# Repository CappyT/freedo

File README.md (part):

# freedo

A local coordinator for tado V3+ 868 MHz heating devices, with a Home Assistant integration.

This is heavily AI-assisted work. The code and the documentation were written largely with AI assistance, under the direction of the project owner. Behavior was checked with automated tests, and on a real plant only where the [Status](#status) section says so.

## Contents

- [What it is](#what-it-is)
- [Status](#status)
- [Scope and limits](#scope-and-limits)
  - [Supported devices](#supported-devices)
- [Compared with the tado cloud and HomeKit](#compared-with-the-tado-cloud-and-homekit)
- [Requirements](#requirements)
- [Install](#install)
- [First setup](#first-setup)
- [Dashboard](#dashboard)
- [Features](#features)
- [Safety](#safety)
- [Community](#community)
- [Documentation](#documentation)
- [Development](#development)
- [Legal](#legal)
- [Licence](#licence)

## What it is

freedo replaces the tado internet bridge for the radiator valves and wall thermostats that it
coordinates. The coordinator is a Go daemon. It talks over a serial link to an ESP32 with a CC1101
radio, and it serves a local HTTP API. A Home Assistant integration uses that API. The daemon
keeps the plant under local control, with no cloud.

freedo is not a way to use the tado app or the tado cloud. See [Scope and limits](#scope-and-limits).

freedo is not affiliated with tado. tado is a trademark of its owner. This project uses the
name only to describe which devices it works with. See [Legal](#legal) for the legal basis of the
project.

## Status

freedo is experimental. Expect bugs, and keep a way to control the heating by hand.

Tested on a real plant (one plant, one ESP32 development board with one CC1101 module):

- Reception and decoding of device reports (temperature, demand, boiler values, battery), and the MAC and CSL
  exchange with the bridge firmware.
- Setpoint, boost and return-to-program writes to a valve.
- Home and away: in use on the plant, and the valves follow.
- A weekly schedule: the rooms follow its blocks, and a schedule edited in the dashboard reaches the valves.
- The child lock of a valve: in use on the plant.
- Hot water on, off and temperature writes to the wall thermostat.
- A fixed flow limit, read back from the boiler through the OpenTherm values the thermostat reports.
- Identify on a valve and on the wall thermostat.
- The display orientation and the change notice of a valve.
- The motor calibration, on one valve.
- The temperature correction in the modes `config` and `dbg2`, on one valve.
- A window state that the coordinator sets, on one valve.
- A window that the wall thermostat detected: its report, the block that reaches the thermostat and the
  valve of the same room, the close after the window time, and a reset that ends the window before that
  time. No window that a valve detected was seen: with one sample each 10 to 16 minutes, a valve did not
  report an open window in 40 minutes.
- The warning for a valve that is not mounted. It raised no fault alert, and it cleared after the valve
  was mounted.
- Pairing one valve through the API: the button press that makes the valve leave, the removal from the
  installation, the pair window of the bridge firmware, the declaration of a device that the installation
  did not hold, the `d/pair` command and the serial that the daemon learns from the device. The valve
  works in its zone again. A remote leave command was tried on that valve and had no effect.
- Pairing the same valve from the dashboard, two times. The last version of the page Add device, with no
  default room and with the end state, did not run on the plant.
- On the page Rooms and devices: a room created, its options saved and the room deleted, a device moved
  from No room to a room, a device removed, and a valve restarted. The valve joined again by itself about
  40 seconds after the command.
- The add-on freedo beta: the move from the add-on freedo, with the copy of the state that the add-ons
  made by themselves up to 0.7.0. Every device talked to the beta add-on in three minutes. The return
  to the add-on freedo did not run with that copy.
- The backup of the dashboard: a download as a Home Assistant administrator with no token, a restore
  of that file in the same add-on, and the return from freedo beta to the add-on freedo with a
  restore there. The daemon kept the replaced state, restarted by itself, waited 250 seconds and
  talked to every device again with no decryption error. The countdown that the dashboard shows
  during that wait did not run on a plant.
- The read of the firmware version of each device.
- freedo runs as the only coordinator of that plant, as a Home Assistant add-on with the integration.
  The devices of that plant were not paired from scratch, apart from one valve.
- The dashboard commands for setpoint, boost, off, home and away, and the programs.

Tested only with automated tests and synthetic fixtures:

- Away temperatures, away programs and the end rule `until_auto_change`.
- A network that starts with no paired device, and the pairing of a wall thermostat.
- A window that a valve detects.
- The Router Advertisement gateway and DNS addresses (`router_gateway`, `router_dns`) and the zone
  configuration of a heating zone with no circuit.
- A schedule document with several day programs, the program profiles and the offline schedule
  (devices run the program alone).
- Firmware transfer to a device. No block was ever sent on air.
- Early start, the weather curves (your own and the default curve), automatic flow adaptation, the
  external room temperature, the automatic correction and the controller gain suggestion.
- The energy and gas estimate against the gas meter of the plant, over 8 days: the meter counted
  7.07 m3 and the estimate 7.38 m3, 4.4 % high. The daemon learned a correction factor of 0.958. The
  meter also counts any other gas user on it. A third reading checks that the factor holds.
- The web dashboard. `npm test` covers the API client and the schedule editor logic. `npm run prefix-check`
  and `npm run ui-check` start the daemon with no radio and a seeded synthetic installation. They open each
  page in headless Chrome under a path prefix, and drive the schedule editor, the presence switch, the
  child lock, Turn off, the profiles, the rename of a device, the page Rooms and devices (a room, a
  pairing, a move, a removal, a restart, a circuit), the options of a room, the boiler fault codes and the
  first setup on an empty database. The page First setup did not run on a plant that starts empty.
- The boiler fault codes in the dashboard and in Home Assistant. No real boiler fault was seen.
- In the integration: the reload after a change of the installation, the service `freedo.pair` and the
  event entity Alert.
- The six blueprints: presence, season profile, alert notification, distance setback, auxiliary heat and
  valve exercise.

No record covers a long run or a long outage of the coordinator.

## Scope and limits

- freedo replaces the tado internet bridge and the tado cloud for the devices it coordinates.
  It does not connect to the tado cloud in place of the bridge. The tado app does not work with a
  plant that freedo runs. This is out of scope.
- Device firmware updates: whether freedo can support them is under evaluation. If it does, you
  supply the firmware images. The project distributes none. The daemon has a transfer route that
  no test on air has used.
- An existing tado plant pairs to freedo from scratch. Each device leaves the commercial bridge and
  joins the network of freedo. The pairing ran on air for one valve. Only automated tests cover a
  network that starts with no paired device. You lose the tado app and the cloud functions for those
  devices. The
  rooms and schedules that you set in the tado app do not move to freedo. You describe the rooms again
  in the dashboard or through the API, and the schedules in the dashboard, Home Assistant or the API. To go back,
  pair the devices to the tado bridge again. That procedure belongs to the tado bridge and is not
  documented or tested here. freedo has no leave command and no remote detach. A device leaves its
  network only when you hold its button.
- A setup import from the tado cloud is planned: rooms, schedules and settings. The devices still pair from
  scratch. It is not available.
- Supported hardware: the valves and the wall thermostats of the V3+ line. Other device types
  (wireless receiver, extension kit, wireless sensor) are not supported, because no capture of
  them exists. See [Supported devices](#supported-devices) for the other tado lines.
- A circuit needs a wall thermostat as its heat source. A heating zone with no circuit gets a zone
  configuration without the circuit tag and without the heat source among the members. No device has
  run this configuration, and the install check warns about such a zone. A plant of valves without a
  wall thermostat is not supported yet.
- The boiler energy estimate needs a boiler that reports its modulation over OpenTherm. A boiler on a
  relay has no estimate yet.
- Geofencing, push notifications and multiple users are not part of the daemon. Home Assistant provides
  them. HomeKit is not implemented.

### Supported devices

freedo replaces the tado Internet Bridge IB01 and pairs each device to its own network. The device
models come from the tado article
[What is a tado° Starter Kit, and what are the differences between versions?](https://support.tado.com/en/articles/3403569-what-is-a-tado-starter-kit-and-what-are-the-differences-between-versions)

| Line | Sold | Devices | tado bridge | freedo |
|---|---|---|---|---|
| V1 | 2012-2014 | Box BX02, temperature sensor TS02 | Gateway GW01 | Not supported: a different system. |
| V2 | 2014-2016 | Smart Thermostat RU01, extension kit BU01 | Bridge GW02 | Not tested. Probably the same radio protocol, see [#25](https://github.com/CappyT/freedo/issues/25). |
| V3 | 2016-2018 | Smart Thermostat RU01, Smart Radiator Thermostat VA01 | Internet Bridge IB01 | Not tested. Probably works: it uses the same bridge as V3+. |
| V3+ | since 2018 | Wired Smart Thermostat RU02, Smart Radiator Thermostat VA02, Wireless Receiver BR02/BP02, Wireless Temperature Sensor SU02 | Internet Bridge IB01 | Valves and wired thermostat supported. Wireless receiver and sensor not supported. |
| tado X | since 2024 | RU04, RU05, VA04, SU04, SU05 and others | Bridge X IB02 | Not supported: Thread and Matter use a different radio. |

V2 is probable because tado documents a swap from the GW02 to the IB01 in which the installed
devices reconnect by themselves, and because tado sold the same RU01 with both bridges. Nobody has
tested a RU01 with freedo yet. The RU01 drives the boiler through the extension kit BU01, while
freedo knows the RU02, which drives the boiler over OpenTherm by itself.

## Compared with the tado cloud and HomeKit

The table compares three ways to run a V3+ plant:

- **tado cloud**: the tado Internet Bridge with the tado app. Some automations need the Auto-Assist
  subscription.
- **HomeKit**: the tado Internet Bridge with no internet access. Apple Home or the Home Assistant
  integration HomeKit Device controls it. The tado app does not work in this setup.
- **freedo**: this project, in place of the tado Internet Bridge.

The values in the cells:

- **Yes**: the setup has the function.
- **Auto-Assist**: the tado cloud has the function only with the subscription.
- **Automation**: you build the function yourself, with an Apple Home or Home Assistant automation or a
  third-party integration.
- **Blueprint**: a Home Assistant blueprint that freedo ships.
- **Home Assistant**: a standard function of Home Assistant gives it, with no automation.
- **Partial**: a part of the function is missing. The cell says which part.
- **No**: the setup does not have the function.

The tado columns come from the tado articles
[How does tado° work with Apple HomeKit?](https://support.tado.com/en/articles/3387320-how-does-tado-work-with-apple-homekit),
[What is Auto-Assist?](https://support.tado.com/en/articles/3387221-what-is-auto-assist) and
[What are Quick Actions?](https://support.tado.com/en/articles/4996736-what-are-quick-actions-for-tado-v3).
[Features](#features) gives the test status of each freedo function.

| Function | tado cloud | HomeKit | freedo |
|---|---|---|---|
| Room temperature, humidity and target | Yes | Yes | Yes |
| Off, heat and resume the schedule | Yes | Yes | Yes |
| End rule of a manual change: timer, next block, next automatic change | Yes | Automation. A HomeKit change stays until the schedule resumes. | Yes |
| Boost | Yes, all rooms for 30 minutes | Automation | Yes, one zone or all zones |
| Weekly schedule | Yes | Automation. The schedule set before keeps running, but you cannot change it. | Yes |
| Away schedule for each zone | No | Automation | Yes |
| Program profiles, for example summer and winter | No | Automation | Yes |
| Home and away, with an away temperature for each zone | Yes | Automation | Yes |
| Geofencing | Auto-Assist. Without it, the app asks you to switch. | Automation | Blueprint |
| Preheat before arrival | Auto-Assist | Automation | Blueprint. It reads the distance, not the travel time. |
| Early start | Yes | No | Yes |
| Open window detection | Yes. Without Auto-Assist, the app asks you to switch the heating off. | Automation, with a contact sensor | Yes, from the valves or from a contact sensor |
| Hot water: on, temperature, schedule | Yes | No | Yes |
| Room temperature from another sensor | No | Automation, with a third-party integration | Yes |
| Auxiliary heat from another climate device | No | Automation | Blueprint |
| Child lock, temperature offset, valve calibration, identify | Yes | No | Yes |
| Flow temperature limit | Yes | No | Yes |
| Flow temperature from the weather | Auto-Assist | No | Yes, with a local curve and controller |
| Boiler data and fault codes | Partial. Care & Protect tells you that the boiler has a fault, with no fault code. | No | Yes. OpenTherm now, the other boiler buses when their integration is complete. |
| Energy and gas report | Auto-Assist | No | Yes, from the boiler modulation, corrected by meter readings |
| History | 1 day. 13 months with Auto-Assist. | Home Assistant, with no heating report | Yes, in the daemon and in Home Assistant |
| Air comfort | Auto-Assist, with outdoor air freshness | No | Partial. No outdoor air freshness. |
| Alerts: low battery, device offline, open window | Yes | Automation | Blueprint |
| Several users | Yes | Yes, Apple Home sharing or Home Assistant users | Yes, the Home Assistant users |
| Voice control | Yes: Alexa, Google Assistant, Siri | Yes: Siri | Home Assistant |
| Remote access | Yes | Partial. It needs a home hub (Apple TV, HomePod, iPad) or Home Assistant. | Home Assistant |
| Works without internet | No. The app and the automations need the cloud. | Yes | Yes |
| Subscription | Auto-Assist, for the automations | No | No |
| Rooms, devices and pairing | Yes | No | Yes. Every device pairs again from scratch. |
| Device firmware updates | Yes | No | No |
| Supported devices | All V3+ devices | The heating and cooling rooms of the bridge | V3+ valves and wired wall thermostat |
| Extra hardware | No | No | An ESP32 with a CC1101 radio |
| Maturity | Commercial product | Commercial product | Experimental |

## Requirements

- Radio hardware: an ESP32 with a CC1101 module on a USB port, flashed with the bridge firmware
  in [`firmware/cc1101_bridge`](firmware/cc1101_bridge/README.md). Each release attaches the
  firmware image: see [Flash a released image](firmware/cc1101_bridge/README.md#flash-a-released-image).
  This firmware is almost completely AI-generated. See the [notice](firmware/cc1101_bridge/README.md)
  in its README: it ran on one ESP32 development board with one CC1101 module only.
- A radio board design for the bridge exists in [`hardware/radio`](hardware/radio/README.md). This PCB design is
  almost completely AI-generated and is not tested. See the [notice](hardware/radio/README.md) before you use it.
- A Home Assistant installation (2026.8 or later) or a host that runs a container.
- Go, if you build from source. The version is in `go.mod`.

Use one coordinator per radio network. Switch the commercial bridge off before freedo transmits.

## Install

<details>
<summary><strong>Info installation method</strong></summary>
The freedo service can run as a Home Assistant Add-on (recommended) or a standalone Docker container. 
Both use the same Home Assistant integration.

</details>
Install freedo (Add-On or Docker)

<table>
<tr>
<td width="50%" valign="top">

<details>
<summary><strong>Home Assistant Add-on (recommended)</strong></summary>

The easiest way to run freedo is directly as a Home Assistant Add-on (called an App in recent Home Assistant releases).

1. Add the freedo repository

   Alternative manually:
    <details>
    - Go to **Settings → Add-ons → Add-on Store**.
    - Add Repositories **https://github.com/CappyT/freedo**
    </details>
3. Install and configure freedo

    - Go to **Settings → Add-ons → Add-on Store**.
    - Search for **freedo** and install it.
    - Go to **freedo → Configuration**.
    - Enable **Show unused optional configuration options**.
    - Select the ESP32 serial port and click **Save**.
    - Go to **Info** and start freedo with **Protection Mode enabled**.

    The add-on starts in dry-run mode.

</details>

</td>
<td width="50%" valign="top">

<details>
<summary><strong>Standalone Docker container</strong></summary>

Run the freedo service independently of Home Assistant.

This is useful if you run Home Assistant in a container, on a separate machine or without the Home Assistant Supervisor.

The image ghcr.io/cappyt/freedo is available for linux/amd64 and linux/arm64.

1. Prepare the configuration

    sh
    cp docker-compose.example.yml docker-compose.yml
    openssl rand -hex 32 > freedo_api_token

2. Configure the container

    Before starting, edit docker-compose.yml and configure:
    
    The ESP32 serial device.
    The serial device group ID.
    The time zone (TZ).
    
    Without TZ, the container runs in UTC and the devices receive a UTC offset of 0.

3. Start the container

    sh
    docker compose up -d

The container starts in dry-run mode.

For volume configuration, time zone settings and building from source, see docs/OPERATION.md.

</details>

</td>
</tr>
</table>

<details>
<summary><strong>Install Home Assistant Integration (required for both installation methods)</strong></summary>

1. Add the freedo repository

    Alternative manually:

    <details>
    <summary><strong>Home Assistant 2026.11 and newer (Marketplace)</strong></summary>
    
    Open Settings → Marketplace.
    Add https://github.com/CappyT/freedo as an Integration.
    
    </details>
    
    <details>
    <summary><strong>Home Assistant versions before 2026.11 (HACS)</strong></summary>
    
    Open HACS → menu → Custom repositories.
    Enter https://github.com/CappyT/freedo.
    Select Integration and add the repository.
    
    </details>

2. Download and install freedo integration

    - Go to **HACS / Marketplace → Integrations**.
    - Search for **freedo** and click **Download**.
    - Restart Home Assistant.

4. Connect to the freedo integration with freedo(Add-On or Docker) 

    Home Assistant Add-on:
       Confirm the automatic discovery notification. It provides the host, port and token.
    Docker container:
       Go to Settings → Devices & services → Add integration → freedo. Enter the host, port and API token manually.

</details>

<details>
<summary><strong>Home Assistant Blueprints (optional)</strong></summary>

Import the available freedo automations directly into Home Assistant:

| Blueprint | Import |
|---|---|
| Notifications and alerts (including low battery) |  |
| Presence Away |  |
| Season Profile |  |
| Distance Setback |  |
| Auxiliary Heat |  |
| Valve Exercise |  |

</details>

<details>
<summary><strong>Stable and experimental versions</strong></summary>

The freedo add-on and integration follow two release channels:

Stable: Tags vX.Y.Z. The freedo add-on and HACS offer these versions by default.
Experimental: Pre-release tags such as vX.Y.Z-beta.N, which receive less testing on a real plant.

HACS offers experimental integration versions when beta versions are enabled for the freedo repository.

The repository also provides a second add-on, freedo beta, which runs experimental versions. It has its own data.

To move between the stable and beta add-ons:

Create a backup in the Settings page of the currently installed add-on.
Stop the currently running add-on.
Start the other add-on.
Restore the backup there.

The same procedure applies when switching back. The two add-ons must never run at the same time.

See addon-beta/DOCS.md for details about switching between versions.

Pre-release container images also carry the corresponding version tag and beta suffix.

</details>

Additional documentation
addon/DOCS.md – Add-on options, data and backups.
addon-beta/DOCS.md – Beta add-on and migration.
docs/OPERATION.md – Docker configuration and operation.
custom_components/freedo/README.md – Integration entities, services and blueprints.

## First setup

The page First setup of the [dashboard](#dashboard) shows these steps with their live state.

1. Start the daemon in dry-run and read its log.
2. Check `GET /api/health`. The field `mode` must be `live`. The field `calibrated` turns `true` once
   the radio has calibrated itself on the frames of the first paired device; until then the radio works
   on FSCTRL0 0x34, the start register. See [Radio calibration](docs/OPERATION.md#radio-calibration). The field `timezone.name` must be the
   time zone of the plant. If `timezone.fallback` is `true`, the daemon uses the zone of its host: set
   the time zone on the page, or see [Time zone](docs/OPERATION.md#time-zone).
3. Add the rooms, on the page or through the API under `/api/install`. The daemon creates a network key
   and a coordinator identity at the first start.
4. Switch the commercial bridge off and add `--tx` (or the add-on option Transmit).
5. Pair the devices, on the page or as described in [`docs/OPERATION.md`](docs/OPERATION.md#pairing-a-device).
6. Add the heating circuit, on the page or through the API.

The calibration, the serial port, `--tx` and the commercial bridge stay outside the page.

## Dashboard

The daemon serves a web interface at its HTTP address. It shows the zones, the hot water, the boiler and
the devices. It sets temperatures with the four end rules, boosts a zone and switches it off. It switches
the home between home and away. It edits the home and away schedules, and it creates, renames, deletes and
activates the program profiles. It sets the flow limit, renames a device, locks a valve and identifies a
device. It resets an open window of a room, also one that a valve detected. It shows the fault codes of
the boiler on the page Boiler and in a banner on every page. It has English, Italian, German and French texts and a light and a dark theme.

The screenshots show a test installation with invented data.

- Container: open `http://<host>:8080/` and enter the API token once.
- Home Assistant add-on: select Open Web UI, or the entry freedo in the sidebar. The page needs no token.

The page Rooms and devices manages the installation. It creates, renames and deletes rooms. It adds a
heating circuit, changes its heat source and deletes it. In the settings of a room it renames, moves, restarts and removes a
device of that room, and it sets the circuit, the measuring device and the demand reporter. The devices in no
room form the group No room, with the same settings. It adds a device: it opens the pair window, declares
the device that the window hears and sends the pair command. A removal shows the effects before you confirm. Under Home Assistant ingress this
page and the page First setup need no token, so every Home Assistant user who can open the dashboard can
change the installation and pair a device. The network key, the identity of the network,
the kind and the serial of a device, the controller gains of a room and the name of a circuit stay in
the API. The settings of a heated room hold its options: the device or the Home Assistant thermometer
that measures the room, window detection, away temperature, the end rule of a change made on a device,
early start, offset and offset mode. See
[`docs/OPERATION.md`](docs/OPERATION.md#dashboard) for the access rules and
[`dashboard/README.md`](dashboard/README.md) to build it.

## Features

The table compares the functions of the tado app with freedo. "equal" means the function exists in the
daemon, or in the integration and the blueprints that freedo ships, and has automated tests. The note
says when a function needs Home Assistant. "partial" means a part of the function is missing.
"extra" means the tado app has no such function. "not implemented" means freedo has none. The notes name
what is not verified on air. The routes are in [`docs/API.md`](docs/API.md). The entities are in
[`custom_components/freedo/README.md`](custom_components/freedo/README.md).

| Function | Status | Notes |
|---|---|---|
| Manual change with the four end rules: manual, timer, until the next block, until the next automatic change | equal | `until_auto_change` writes `6240=1`, captured for rooms. No capture holds the end of that overlay. For hot water the value is not verified. |
| Switch a zone off | equal | The form "off until the next block" is captured. The manual form is not. |
| Resume the program, for a zone or for the whole home | equal | |
| Boost for a zone or for all zones | equal | Home Assistant sends one command for each zone. |
| Weekly schedule and copy | equal | In use on one plant: the rooms follow the blocks, and an edit reaches the valves. Several day programs in one document are not verified on air. |
| Home and away | equal | The write shapes come from a capture. In use on one plant: the valves follow. |
| Away temperature for each zone | equal | 5 C means off in away, as in the cloud. Hot water takes no away temperature: it is off in away unless it has an away schedule. Not verified on air. |
| Away schedule for each zone | extra | A zone with an away schedule follows it while the home is away, hot water included. No capture holds this write shape. Not verified on air. |
| Program profiles | extra | A profile holds the home and away schedules of every zone. One profile is active. The dashboard and Home Assistant switch it, and a blueprint switches it by season. Not verified on air. |
| Preheat before arrival | partial | Two blueprints. One ends away when a person enters an approach zone. One sets the away temperature of each room in steps with the distance of the nearest person. Both read a distance and no travel time, and every room gets the same steps. They need Home Assistant. |
| Early start | equal | The daemon learns the heating rate of each zone. No firmware does this. Not verified on air. |
| Geofencing | equal | A blueprint uses the presence of Home Assistant for the whole home, and a second one uses the distance of the nearest person. Needs Home Assistant: the daemon has no geofencing code. |
| Open window detection | equal | The valves detect the window. The detection and its time are room options. A reset from the dashboard or from Home Assistant ends a window of any source. A contact sensor that closes ends only its own hold. On one plant the wall thermostat detected a window and a reset ended it. No detection by a valve was observed. |
| Hot water: on, temperature, program | equal | The daemon keeps the program and writes the thermostat at each block change. |
| Child lock | equal | Valves only. The wall thermostat firmware has no child lock. In use on one plant. |
| Identify a device | equal | Valves and the wall thermostat in a zone. The thermostat shows "Hi!" on its display. |
| Display orientation and change notice | equal | A full `d/config` write homes the valve motor, as with the commercial bridge. |
| Valve calibration | equal | The command comes from firmware and ran on one valve. A `2.xx` answer does not guarantee the stroke. |
| Temperature correction | equal | Two modes. `config` homes the motor. `dbg2` ran on one valve and is in no capture. A Home Assistant automation or Better Thermostat can write the correction from a sensor through the Offset number entity. |
| Room temperature from an outside sensor | extra | Home Assistant chooses for each room a device of the room or the sensor. With the sensor the coordinator owns the zone (next row), and the controller and the learners read the sensor. A room that a device measures ignores the sensor: the daemon answers 409 and Home Assistant lists the room in a repair issue. |
| Coordinator as zone owner | extra | The zone document names the daemon as owner and measuring endpoint. The daemon runs the valve controller on the outside sensor, serves the measure on `z<N>` and pushes it to the members every minute. The valves of the zone lose the election (role `0x05`), follow the pushed demand and the wall thermostat reads the measure from the daemon. Runs on one plant on six rooms, a zone with two valves and a zone with the wall thermostat included. |
| Manage rooms and devices | equal | The dashboard creates, renames and deletes rooms, creates and deletes circuits, moves and renames devices, and sets the measuring device, the demand reporter and the room options. Home Assistant has the same room options and maps each room to an area. The controller gains, the network key and the identity of the network are in the API only. No device reports the offset that it holds, so the dashboard does not show it. A device declared without a serial takes it from its first request. Home Assistant follows a change within one poll. The page Rooms and devices is in use on one plant. |
| Interface | equal | A web dashboard on the daemon monitors and controls the zones, the hot water, the boiler and the devices, and manages the schedules, the profiles and the installation. The control pages and the page Rooms and devices are in use on one plant. The page First setup did not run on a plant that starts empty. |
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
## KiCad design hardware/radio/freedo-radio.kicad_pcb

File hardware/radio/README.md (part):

# freedo radio rev A

This PCB design is almost completely AI-generated. I have no experience designing a PCB, this work is not tested and may be completely wrong. If you are willing to help, a pull request is accepted.

Documented checks: an electrical review (findings E01 to E20, outcome in section 8.3) and a silkscreen DRC result (section 6.4). No ERC result is documented.

## State of the files

The repository shows no built board, and every bring-up check in section 8.2 is open. `tools/make_fab.py` generates the fabrication package (gerbers, BOM, placement file) on demand. The package is not committed. It comes from an untested design, so have it reviewed before you order it.

## Licence and provenance

The design files in this directory are under the same licence as the rest of the project (Apache License 2.0, see the `LICENSE` file at the root). The footprints and symbols in `lib/` derive from EasyEDA and LCSC libraries and from Espressif libraries. This is provenance only. The terms of those sources apply to those parts.

## 1. Purpose and scope

Rev A replaces the ESP32 devkit and the CC1101 module with one board.
The board carries an ESP32-S3-MINI-1-N8, an Ebyte E07-900MM10S CC1101 module, a W5500 with a
discrete transformer, an optional isolated PoE module and USB-C.
The host talks to the board over USB (native USB-Serial-JTAG) or, after a firmware port, over Ethernet.
JLCPCB makes the 4-layer PCB and assembles all SMD parts on the top side.
The user hand-solders the RJ45 jack, the DP9900LP-5V module, the edge-mount SMA and, when needed, the J203 header.

Conventions in this file:

- "(unverified)" marks a value that no document in hand confirms.
- Class: B = JLC Basic, P = JLC Preferred (Extended without the loading fee), E = Extended.
- Fit: yes = fitted on every board, opt = hand-soldered only on PoE boards, DNP = footprint only.
- Class and stock come from a JLC parts database snapshot of 2026-09-24. Check them again at BOM upload.
- Designators: the RF block uses U1, J1, L1, C1, C2 and 1xx. MCU/USB/power uses 2xx, Ethernet 3xx, PoE 4xx.

## 2. Block diagram

```
 LINE SIDE (PoE)                     ||   SYSTEM SIDE
                                     ||
 J301 RJ45 -- pairs 1/2, 3/6 --[ T301 B1608S ]-- MDI -- U301 W5500 -- SPI GPIO 9-14 ----------------+
   |             | line CTs 15, 10   ||                   | Y301 25 MHz                             |
   | 4/5, 7/8    |                   ||                                                             |
 BR401 MB10S   BR402 MB10S           ||                                                             |
   +------+------+                   ||                                                             |
          | VIN+/VIN-, D401 SMAJ58A  ||                                                             |
     [ U401 DP9900LP-5V, isolated  ]-- +VDC 5.66 V -- D402 SS34 --------------+                     |
 Bob Smith: 4 x (75R + 10 nF)        ||                                       |                     |
 -> C322 -> SHIELD -> C323 -> GND    ||  J201 USB-C -- F201 -- D201 -- D202 --+ 5V_SYS              |
                                     ||       | D+/D- via U202 (no VBUS pin)  |                     |
                                              | VBUS -> R216/R217 -> GPIO17   U203 TLV76133DCYR     |
                                              |                               | 3V3                 |
                                              +-- USB GPIO 19/20 ------> U201 ESP32-S3-MINI-1-N8 <-+
                                                                   J203 ----> | SPI GPIO 36-42
                          +---------------------------------------------------+
   3V3 -- L1 -- 3V3_RF -- U1 E07-900MM10S -- ANT -- R191 0R -- L191 shunt -- J1 SMA (edge)
```

PoE option: only U401 is optional. JLC fits the SMD PoE parts on every board, because one order has one BOM (section 5.4).

## 3. Pin map

Module pads from the ESP32-S3-MINI-1 datasheet v1.7, Table 3-1 (pdf p.11-12).

| Signal | GPIO | Pad | Dir | Circuit |
| --- | --- | --- | --- | --- |
| W5500 RSTn | 9 | 13 | out | R313 10k pull-up to 3V3 |
| W5500 INTn | 10 | 14 | in | R314 10k pull-up to 3V3 |
| W5500 MOSI | 11 | 15 | out | direct |
| W5500 MISO | 12 | 16 | in | direct |
| W5500 SCLK | 13 | 17 | out | R208 33R at the module |
| W5500 SCSn | 14 | 18 | out | W5500 internal pull-up (50-112k) |
| Radio GDO2 (E22 DIO1) | 36 | 32 | in | direct, TP106 |
| Radio GDO0 (E22 DIO3) | 37 | 33 | in | direct, TP105 |
| Radio SCLK | 39 | 35 | out | R209 33R at the module, TP101 |
| Radio CSn (E07 CSN, E22 NSS) | 40 | 36 | out | R210 10k pull-up to 3V3_RF, TP104 |
| Radio SI (MOSI) | 41 | 37 | out | direct, TP102 |
| Radio SO (E07 MISO/GDO1, E22 MISO) | 42 | 38 | in | direct, TP103 |
| E22 NRST (option) | 21 | 25 | out | R101 0R DNP to U1 pad 3 |
| E22 RXEN (option) | 47 | 27 | out | R102 0R DNP to U1 pad 10 |
| E22 BUSY (option) | 48 | 30 | in | R103 0R DNP to U1 pad 11 |
| VBUS_SENSE | 17 | 21 | in | R216 68k from VBUS, R217 100k and C209 100 nF to GND |
| I2C SDA | 15 | 19 | io | J203-2, R219 4.7k to 3V3 DNP |
| I2C SCL | 16 | 20 | io | J203-3, R220 4.7k to 3V3 DNP |
| Header IO1 (ADC1_CH0) | 1 | 5 | io | J203-4 |
| Header IO2 (ADC1_CH1) | 2 | 6 | io | J203-5 |
| Header IO7 (ADC1_CH6) | 7 | 11 | io | J203-6 |
| Header IO8 (ADC1_CH7) | 8 | 12 | io | J203-7 |
| LED TX | 4 | 8 | out | R212 1k, D204 to GND |
| LED RX | 5 | 9 | out | R213 1k, D205 to GND |
| LED STATUS | 6 | 10 | out | R214 1k, D206 to GND |
| USB D- | 19 | 23 | io | R203 22R, U202, J201 A7/B7 |
| USB D+ | 20 | 24 | io | R204 22R, U202, J201 A6/B6 |
| UART0 TX (U0TXD) | 43 | 39 | out | R207 1k at the module, TP211, J203-8 |
| UART0 RX (U0RXD) | 44 | 40 | in | TP212, R218 1k to J203-9 |
| BOOT | 0 | 4 | in | R206 10k pull-up, SW202 to GND |
| EN (CHIP_PU) | - | 45 | in | R205 10k pull-up, C201 1 uF, SW201 to GND |
| 3V3 | - | 3 | pwr | C206 22 uF + C207 100 nF at the pad |
| GND | - | 1, 2, 42, 43, 46-65 | pwr | 46-60 is the antenna-end row, 61 the EPAD, 62-65 the corner pads |
| Not connected | 3, 45, 46, 26 | 7, 41, 44, 26 | - | Straps (3, 45, 46) and PSRAM CS (26) |
| Not connected | 33-35 | 28, 29, 31 | - | Octal flash lines, free on the N8 |
| Spare, not connected | 18, 38 | 22, 34 | - | GPIO38 is driven low in USB-OTG download (see below) |

GPIO allocation rules for the new signals:

- No strapping pin (GPIO0, 3, 45, 46), no USB pin (19, 20), no used pin.
- No flash or PSRAM line: GPIO26-32 are priority 4 (S3 DS v2.2 2.3.5, pdf p.26). GPIO33-37 are priority 3: they
  are the octal lines DQ4-DQ7 and DQS (S3 DS Table 2-14, pdf p.31). The N8 has quad flash (MINI-1 DS Table 1-1), so
  GPIO36 and GPIO37 carry GDO2 and GDO0.
- The free priority-2 pins with a MINI-1 pad are GPIO1, 2, 7, 8, 15-18, 21, 47, 48 (S3 DS 2.3.5 Table 2-9,
  MINI-1 DS Table 3-1). Ten of the eleven are used. GPIO18 stays spare.
- The four header GPIOs are ADC1 pins: GPIO1, 2, 7, 8 = ADC1_CH0, CH1, CH6, CH7 (MINI-1 DS Table 3-1).
- I2C uses GPIO15/16. They show the 60 us low power-up glitch too (HDG 1.3.10 Table 10, XTAL_32K_P/N): a device on
  J203 can see a false START. Send a bus recovery (9 clocks, then STOP) before the first transfer.
- VBUS_SENSE uses GPIO17. Its 60 us power-up low glitch drives into 40 kohm and is harmless.
- The E22 lines use GPIO21, 47 and 48, the free pads nearest to the radio pads 32-38.
- Both SPI buses are planar. The GPIO order follows the pad order of U201, U301 and U1 (section 6.4), so every
  line routes on F.Cu without a crossing. W5500: pads 13-18 against U301 pins 37-32. Radio: pads 32-38 against
  U1 pads 20, 18, 15, 14, 13, 12. Pad 34 (GPIO38) stays spare: its USB-OTG download level (low) would fight a
  radio output.

Boot states of the bus pins. At reset, no pin in the table has a pull or an output (S3 DS Table 2-1, pdf p.16-17).
After reset, each is an input (IE). GPIO39 also gets the weak pull-up while pad JTAG is not disabled (note 7).

| GPIO | Signal | ESP32 side | Power-up glitch | SPI boot | USB-OTG download |
| --- | --- | --- | --- | --- | --- |
| 9 | W5500 RSTn | out | 60 us low | input | input |
| 10 | W5500 INTn | in | 60 us low | input | input |
| 11 | W5500 MOSI | out | 60 us low | input | input |
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
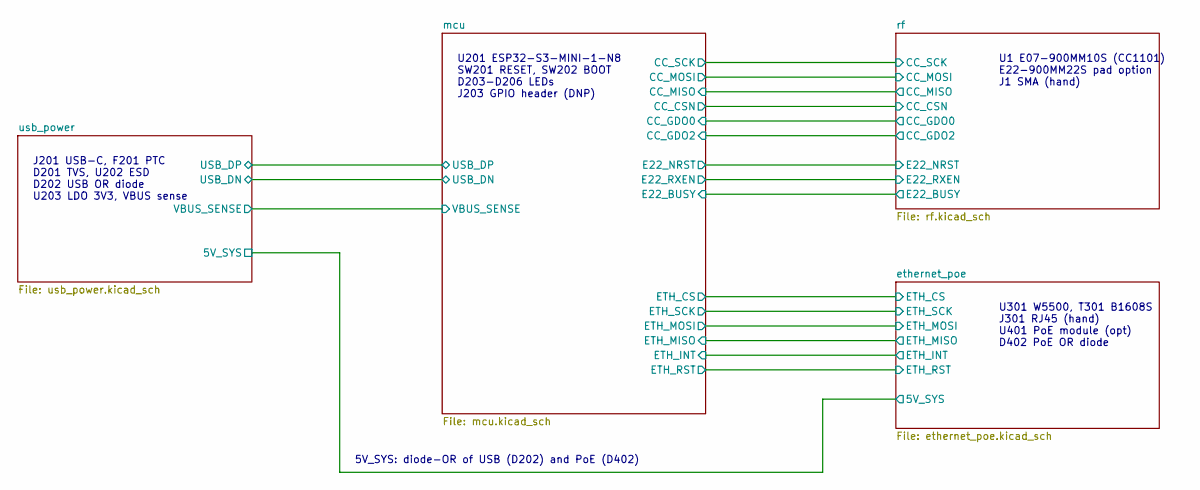
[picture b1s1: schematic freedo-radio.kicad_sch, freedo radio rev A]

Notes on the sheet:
J201 USB-C, F201 PTC D201 TVS, U202 ESD D202 USB OR diode U203 LDO 3V3, VBUS sense
U201 ESP32-S3-MINI-1-N8 SW201 RESET, SW202 BOOT D203-D206 LEDs J203 GPIO header (DNP)
U1 E07-900MM10S (CC1101) E22-900MM22S pad option J1 SMA (hand)
U301 W5500, T301 B1608S J301 RJ45 (hand) U401 PoE module (opt) D402 PoE OR diode
5V_SYS: diode-OR of USB (D202) and PoE (D402)

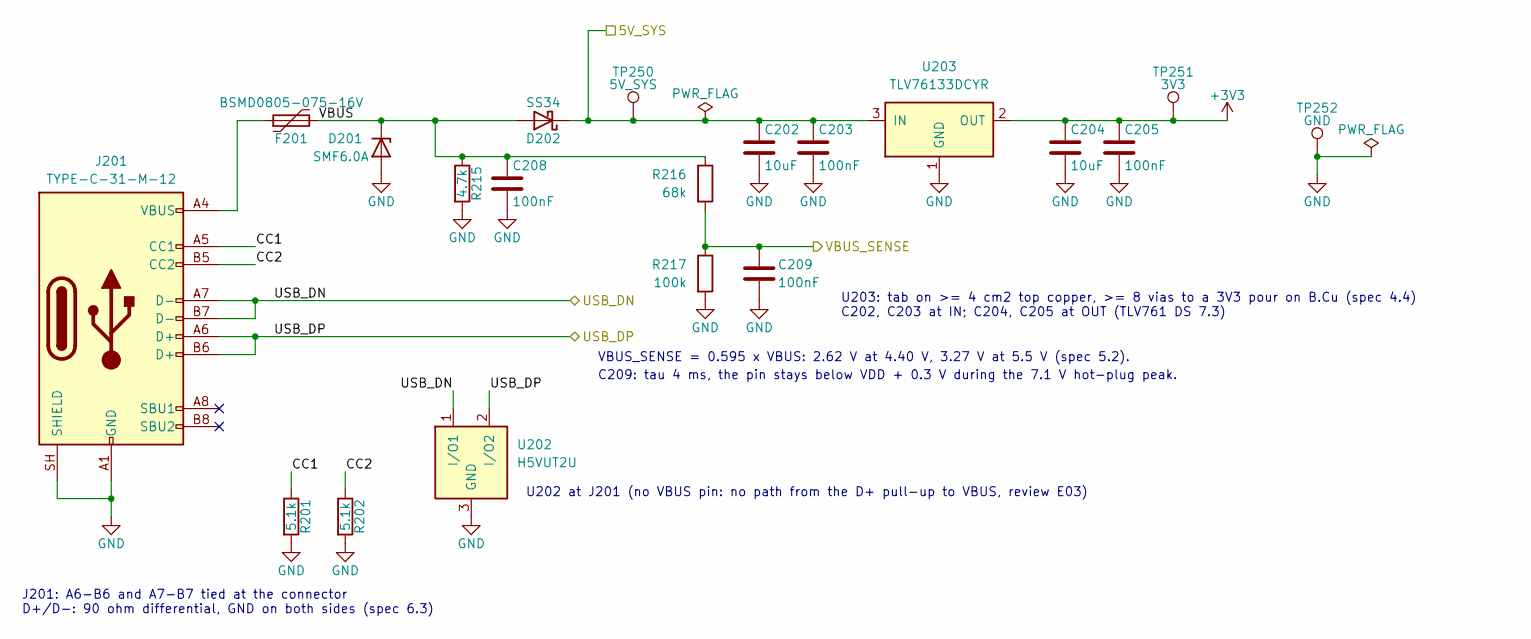
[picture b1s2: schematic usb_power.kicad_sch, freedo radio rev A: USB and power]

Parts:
C202: 10uF; C_0805_2012Metric; MPN CL21A106KAYNNNE; LCSC C15850
C203, C205, C208, C209: 100nF; C_0603_1608Metric; MPN CC0603KRX7R9BB104; LCSC C14663
C204: 10uF; C_0603_1608Metric; MPN CL10A106KP8NNNC; LCSC C19702
D201: SMF6.0A; SOD-123FL_L2.7-W1.8-LS3.8-RD; MPN SMF6.0A; LCSC C19077499
D202: SS34; SMA_L4.3-W2.6-LS5.2-RD; MPN SS34; LCSC C8678
F201: BSMD0805-075-16V; F0805; MPN BSMD0805-075-16V; LCSC C976303
J201: TYPE-C-31-M-12; HRO_TYPE-C-31-M-12; MPN TYPE-C-31-M-12; LCSC C165948
R201, R202: 5.1k; R_0603_1608Metric; MPN 0603WAF5101T5E; LCSC C23186
R215: 4.7k; R_0603_1608Metric; MPN 0603WAF4701T5E; LCSC C23162
R216: 68k; R_0603_1608Metric; MPN 0603WAF6802T5E; LCSC C23231
R217: 100k; R_0603_1608Metric; MPN 0603WAF1003T5E; LCSC C25803
TP250: 5V_SYS; TestPoint_Pad_D1.5mm
TP251: 3V3; TestPoint_Pad_D1.5mm
TP252: GND; TestPoint_Pad_D1.5mm
U202: H5VUT2U; SOT-23-3_L2.9-W1.5-P1.90-LS2.6-BR; MPN H5VUT2U; LCSC C20615824
U203: TLV76133DCYR; SOT-223-4_L6.5-W3.5-P2.30-LS7.0-BR; MPN TLV76133DCYR; LCSC C7527500

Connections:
+3V3: C204.1, C205.1, TP251.1, U203.2 (OUT), U203.4 (OUT); also elsewhere on the board
/ethernet_poe/5V_SYS: C202.1, C203.1, D202.1 (K), TP250.1, U203.3 (IN); also elsewhere on the board
/mcu/VBUS_SENSE: C209.1, R216.2, R217.1; also elsewhere on the board
/usb_power/CC1: J201.A5 (CC1), R201.1
/usb_power/CC2: J201.B5 (CC2), R202.1
/usb_power/USB_DN: J201.A7 (D-), J201.B7 (D-), U202.1 (I/O1); also elsewhere on the board
/usb_power/USB_DP: J201.A6 (D+), J201.B6 (D+), U202.2 (I/O2); also elsewhere on the board
/usb_power/VBUS: C208.1, D201.1 (K), D202.2 (A), F201.2, R215.1, R216.1
GND: C202.2, C203.2, C204.2, C205.2, C208.2, C209.2, D201.2 (A), J201.A1 (GND), J201.A12 (GND), J201.B1 (GND), J201.B12 (GND), J201.SH (SHIELD), R201.2, R202.2, R215.2, R217.2, TP252.1, U202.3 (GND), U203.1 (GND); also elsewhere on the board
unnamed: F201.1, J201.A4 (VBUS), J201.A9 (VBUS), J201.B4 (VBUS), J201.B9 (VBUS)

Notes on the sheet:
U203: tab on >= 4 cm2 top copper, >= 8 vias to a 3V3 pour on B.Cu (spec 4.4) C202, C203 at IN; C204, C205 at OUT (TLV761 DS 7.3)
J201: A6-B6 and A7-B7 tied at the connector D+/D-: 90 ohm differential, GND on both sides (spec 6.3)
U202 at J201 (no VBUS pin: no path from the D+ pull-up to VBUS, review E03)
VBUS_SENSE = 0.595 x VBUS: 2.62 V at 4.40 V, 3.27 V at 5.5 V (spec 5.2).
C209: tau 4 ms, the pin stays below VDD + 0.3 V during the 7.1 V hot-plug peak.

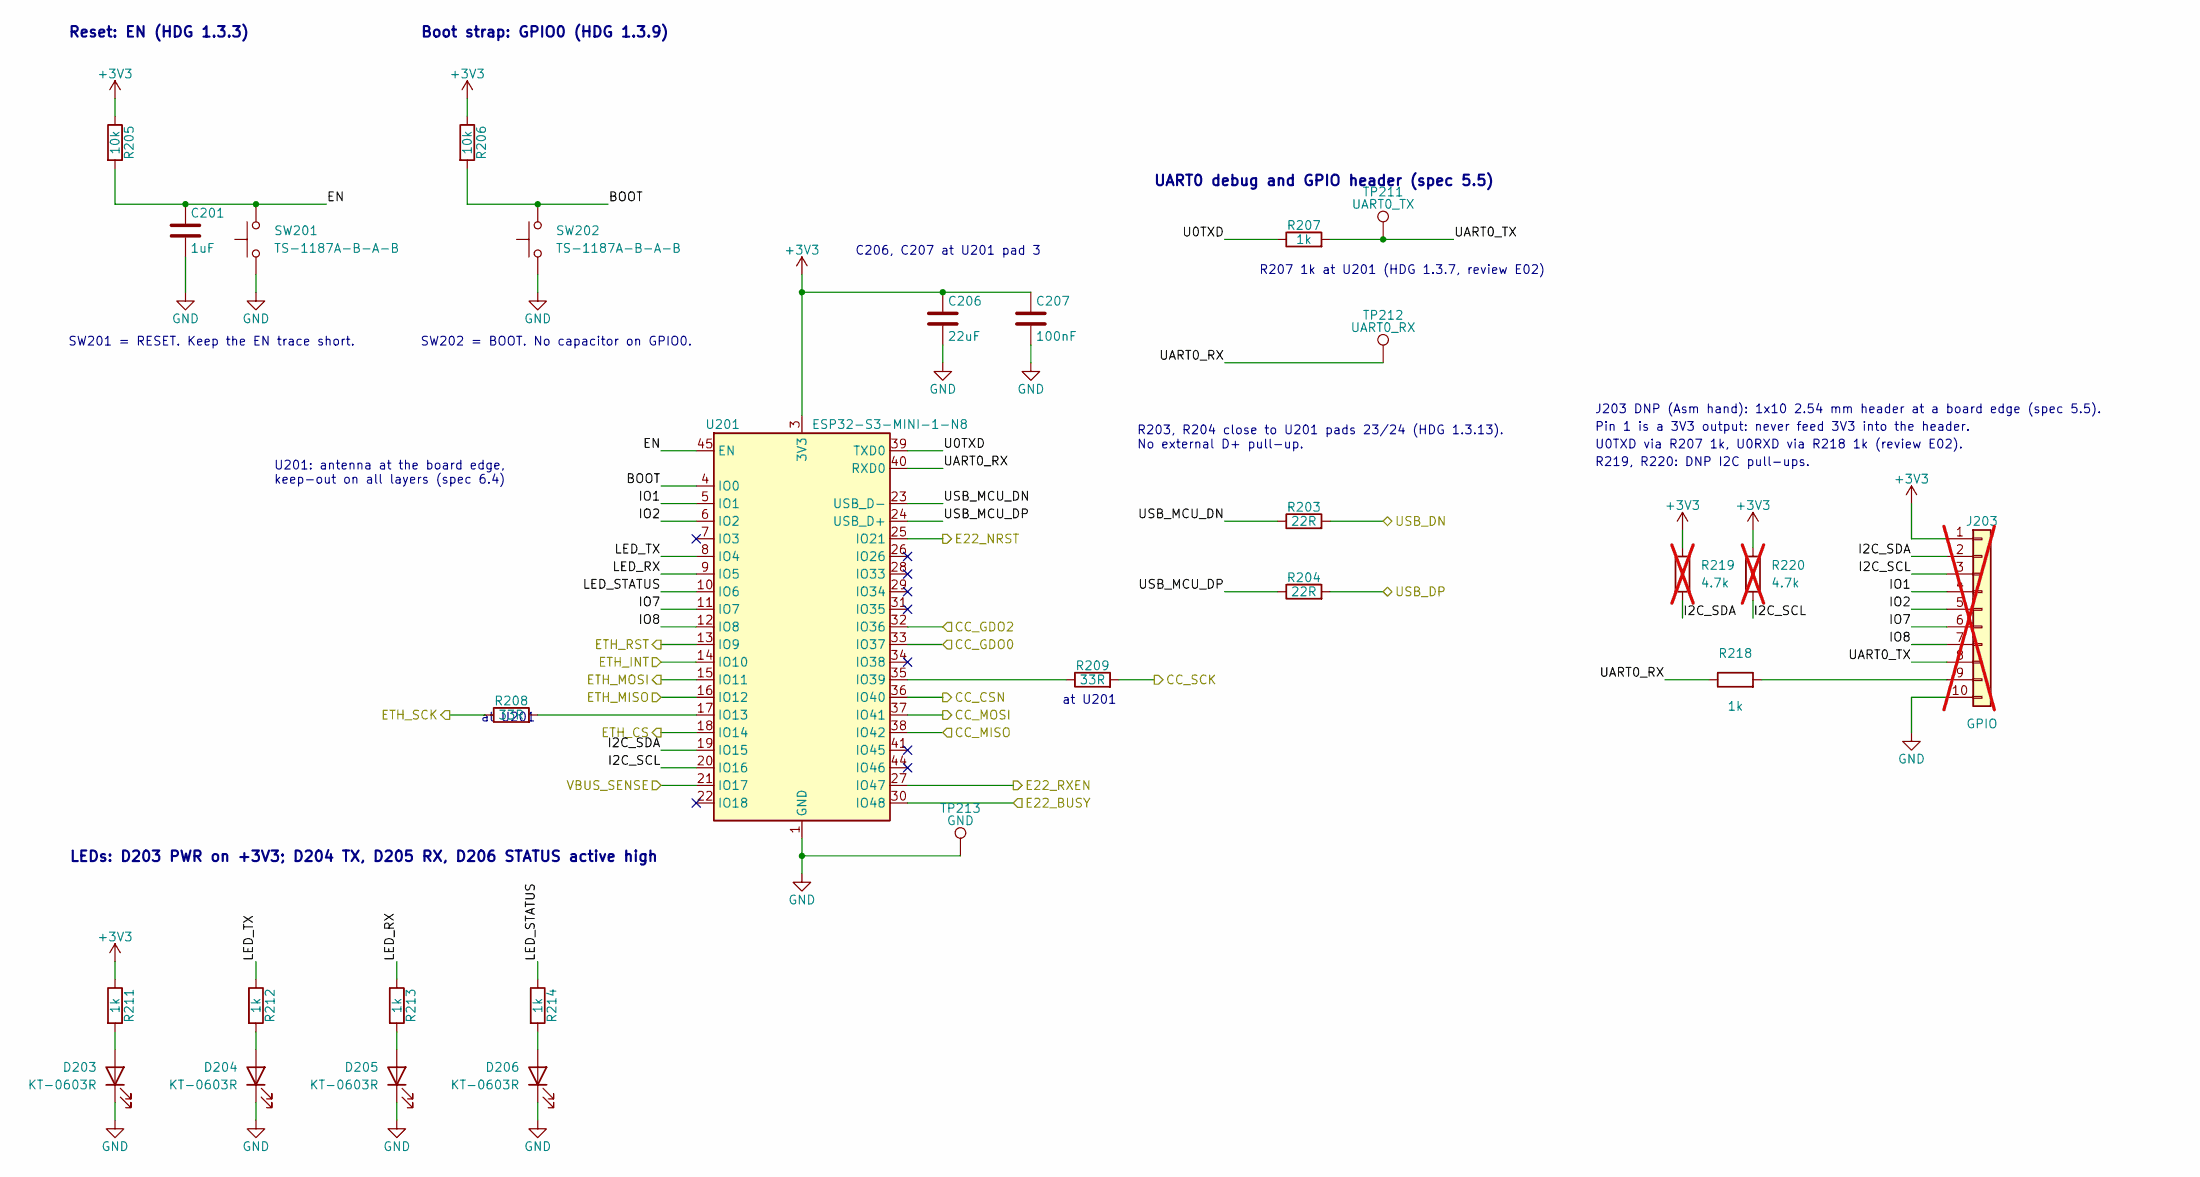
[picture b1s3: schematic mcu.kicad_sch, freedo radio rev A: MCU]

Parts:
C201: 1uF; C_0603_1608Metric; MPN CL10A105KB8NNNC; LCSC C15849
C206: 22uF; C_0603_1608Metric; MPN CL10A226MQ8NRNC; LCSC C59461
C207: 100nF; C_0603_1608Metric; MPN CC0603KRX7R9BB104; LCSC C14663
D203, D204, D205, D206: KT-0603R; LED_0603_1608Metric; MPN KT-0603R; LCSC C2286
J203: GPIO; PinHeader_1x10_P2.54mm_Vertical; not fitted
R203, R204: 22R; R_0603_1608Metric; MPN 0603WAF220JT5E; LCSC C23345
R205, R206: 10k; R_0603_1608Metric; MPN 0603WAF1002T5E; LCSC C25804
R207, R211, R212, R213, R214, R218: 1k; R_0603_1608Metric; MPN 0603WAF1001T5E; LCSC C21190
R208, R209: 33R; R_0603_1608Metric; MPN 0603WAF330JT5E; LCSC C23140
R219, R220: 4.7k; R_0603_1608Metric; MPN 0603WAF4701T5E; LCSC C23162; not fitted
SW201, SW202: TS-1187A-B-A-B; SW_XKB_TS-1187A; MPN TS-1187A-B-A-B; LCSC C318884
TP211: UART0_TX; TestPoint_Pad_D1.5mm
TP212: UART0_RX; TestPoint_Pad_D1.5mm
TP213: GND; TestPoint_Pad_D1.5mm
U201: ESP32-S3-MINI-1-N8; ESP32-S3-MINI-1; MPN ESP32-S3-MINI-1-N8; LCSC C2913206

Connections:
+3V3: C206.1, C207.1, J203.1, R205.1, R206.1, R211.1, R219.1, R220.1, U201.3 (3V3); also elsewhere on the board
/ethernet_poe/ETH_CS: U201.18 (IO14); also elsewhere on the board
/ethernet_poe/ETH_INT: U201.14 (IO10); also elsewhere on the board
/ethernet_poe/ETH_MISO: U201.16 (IO12); also elsewhere on the board
/ethernet_poe/ETH_MOSI: U201.15 (IO11); also elsewhere on the board
/ethernet_poe/ETH_RST: U201.13 (IO9); also elsewhere on the board
/ethernet_poe/ETH_SCK: R208.1; also elsewhere on the board
/mcu/BOOT: R206.2, SW202.2, U201.4 (IO0)
/mcu/CC_CSN: U201.36 (IO40); also elsewhere on the board
/mcu/CC_GDO0: U201.33 (IO37); also elsewhere on the board
/mcu/CC_GDO2: U201.32 (IO36); also elsewhere on the board
/mcu/CC_MISO: U201.38 (IO42); also elsewhere on the board
/mcu/CC_MOSI: U201.37 (IO41); also elsewhere on the board
/mcu/CC_SCK: R209.2; also elsewhere on the board
/mcu/E22_BUSY: U201.30 (IO48); also elsewhere on the board
/mcu/E22_NRST: U201.25 (IO21); also elsewhere on the board
/mcu/E22_RXEN: U201.27 (IO47); also elsewhere on the board
/mcu/EN: C201.1, R205.2, SW201.2, U201.45 (EN)
/mcu/I2C_SCL: J203.3, R220.2, U201.20 (IO16)
/mcu/I2C_SDA: J203.2, R219.2, U201.19 (IO15)
/mcu/IO1: J203.4, U201.5 (IO1)
/mcu/IO2: J203.5, U201.6 (IO2)
/mcu/IO7: J203.6, U201.11 (IO7)
/mcu/IO8: J203.7, U201.12 (IO8)
/mcu/LED_RX: R213.1, U201.9 (IO5)
/mcu/LED_STATUS: R214.1, U201.10 (IO6)
/mcu/LED_TX: R212.1, U201.8 (IO4)
/mcu/U0TXD: R207.1, U201.39 (TXD0)
/mcu/UART0_RX: R218.1, TP212.1, U201.40 (RXD0)
/mcu/UART0_TX: J203.8, R207.2, TP211.1
/mcu/USB_MCU_DN: R203.1, U201.23 (USB_D-)
/mcu/USB_MCU_DP: R204.1, U201.24 (USB_D+)
/mcu/VBUS_SENSE: U201.21 (IO17); also elsewhere on the board
/usb_power/USB_DN: R203.2; also elsewhere on the board
/usb_power/USB_DP: R204.2; also elsewhere on the board
GND: C201.2, C206.2, C207.2, D203.1 (K), D204.1 (K), D205.1 (K), D206.1 (K), J203.10, SW201.1, SW202.1, TP213.1, U201.1 (GND), U201.2 (GND), U201.42 (GND), U201.43 (GND), U201.46 (GND), U201.47 (GND), U201.48 (GND), U201.49 (GND), U201.50 (GND), U201.51 (GND), U201.52 (GND), U201.53 (GND), U201.54 (GND), U201.55 (GND), U201.56 (GND), U201.57 (GND), U201.58 (GND), U201.59 (GND), U201.60 (GND), U201.61 (GND), U201.62 (GND), U201.63 (GND), U201.64 (GND), U201.65 (GND); also elsewhere on the board
unnamed: D203.2 (A), R211.2
unnamed: D204.2 (A), R212.2
unnamed: D205.2 (A), R213.2
unnamed: D206.2 (A), R214.2
unnamed: J203.9, R218.2
unnamed: R208.2, U201.17 (IO13)
unnamed: R209.1, U201.35 (IO39)

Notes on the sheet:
U201: antenna at the board edge, keep-out on all layers (spec 6.4)
C206, C207 at U201 pad 3
Reset: EN (HDG 1.3.3)
SW201 = RESET. Keep the EN trace short.
Boot strap: GPIO0 (HDG 1.3.9)
SW202 = BOOT. No capacitor on GPIO0.
R203, R204 close to U201 pads 23/24 (HDG 1.3.13). No external D+ pull-up.
at U201
R207 1k at U201 (HDG 1.3.7, review E02)
UART0 debug and GPIO header (spec 5.5)
LEDs: D203 PWR on +3V3; D204 TX, D205 RX, D206 STATUS active high
J203 DNP (Asm hand): 1x10 2.54 mm header at a board edge (spec 5.5).
Pin 1 is a 3V3 output: never feed 3V3 into the header.
U0TXD via R207 1k, U0RXD via R218 1k (review E02).
R219, R220: DNP I2C pull-ups.

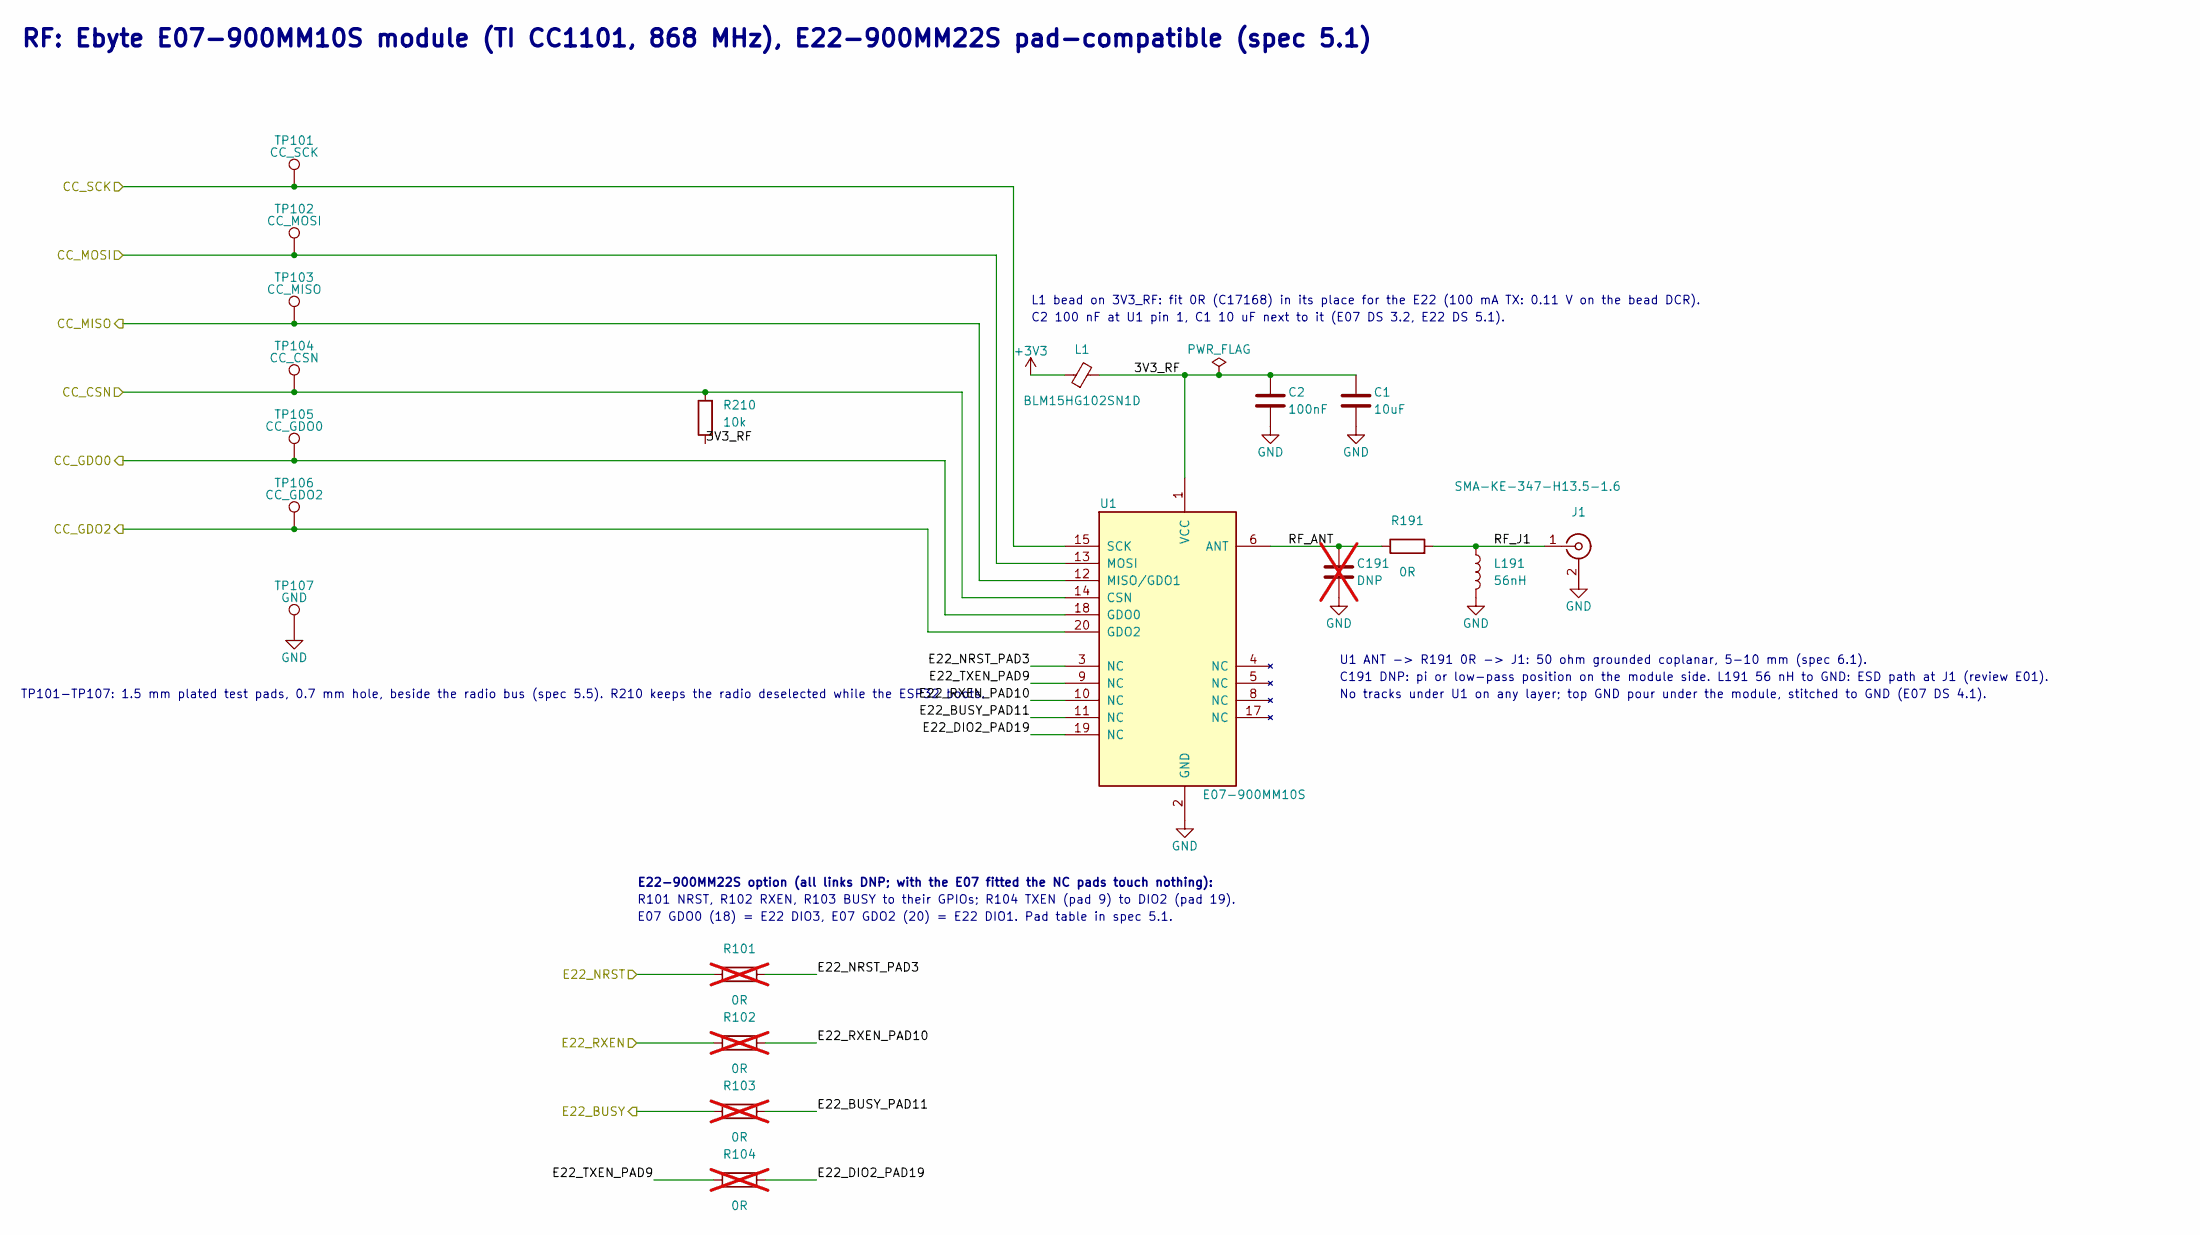
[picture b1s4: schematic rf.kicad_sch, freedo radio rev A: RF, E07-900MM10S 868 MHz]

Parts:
C1: 10uF; C_0603_1608Metric; MPN CL10A106KP8NNNC; LCSC C19702
C2: 100nF; C_0603_1608Metric; MPN CC0603KRX7R9BB104; LCSC C14663
C191: DNP; C_0402_1005Metric; not fitted
J1: SMA-KE-347-H13.5-1.6; SMA_XUNPU_SMA-KE-347-H13.5-1.6_EdgeMount; MPN SMA-KE-347-H13.5-1.6; LCSC C5723200
L1: BLM15HG102SN1D; L_0402_1005Metric; MPN BLM15HG102SN1D; LCSC C76889
L191: 56nH; L_0402_1005Metric; MPN LQW15AN56NG00D; LCSC C167482
R101, R102, R103, R104: 0R; R_0603_1608Metric; MPN 0603WAF0000T5E; LCSC C21189; not fitted
R191: 0R; R_0402_1005Metric; MPN 0402WGF0000TCE; LCSC C17168
R210: 10k; R_0603_1608Metric; MPN 0603WAF1002T5E; LCSC C25804
TP101: CC_SCK; TestPoint_THTPad_D1.5mm_Drill0.7mm
TP102: CC_MOSI; TestPoint_THTPad_D1.5mm_Drill0.7mm
TP103: CC_MISO; TestPoint_THTPad_D1.5mm_Drill0.7mm
TP104: CC_CSN; TestPoint_THTPad_D1.5mm_Drill0.7mm
TP105: CC_GDO0; TestPoint_THTPad_D1.5mm_Drill0.7mm
TP106: CC_GDO2; TestPoint_THTPad_D1.5mm_Drill0.7mm
TP107: GND; TestPoint_THTPad_D1.5mm_Drill0.7mm
U1: E07-900MM10S; Ebyte_LCC-20_10x10mm_P1.27mm_E07-MM10S_E22-MM22S; MPN E07-900MM10S; LCSC C5844212

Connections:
+3V3: L1.1; also elsewhere on the board
/mcu/CC_CSN: R210.2, TP104.1, U1.14 (CSN); also elsewhere on the board
/mcu/CC_GDO0: TP105.1, U1.18 (GDO0); also elsewhere on the board
/mcu/CC_GDO2: TP106.1, U1.20 (GDO2); also elsewhere on the board
/mcu/CC_MISO: TP103.1, U1.12 (MISO/GDO1); also elsewhere on the board
/mcu/CC_MOSI: TP102.1, U1.13 (MOSI); also elsewhere on the board
/mcu/CC_SCK: TP101.1, U1.15 (SCK); also elsewhere on the board
/mcu/E22_BUSY: R103.1; also elsewhere on the board
/mcu/E22_NRST: R101.1; also elsewhere on the board
/mcu/E22_RXEN: R102.1; also elsewhere on the board
/rf/3V3_RF: C1.1, C2.1, L1.2, R210.1, U1.1 (VCC)
/rf/E22_BUSY_PAD11: R103.2, U1.11 (NC)
/rf/E22_DIO2_PAD19: R104.2, U1.19 (NC)
/rf/E22_NRST_PAD3: R101.2, U1.3 (NC)
/rf/E22_RXEN_PAD10: R102.2, U1.10 (NC)
/rf/E22_TXEN_PAD9: R104.1, U1.9 (NC)
/rf/RF_ANT: C191.1, R191.1, U1.6 (ANT)
/rf/RF_J1: J1.1 (In), L191.1, R191.2
GND: C1.2, C2.2, C191.2, J1.2 (Ext), L191.2, TP107.1, U1.2 (GND), U1.7 (GND), U1.16 (GND); also elsewhere on the board

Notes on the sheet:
RF: Ebyte E07-900MM10S module (TI CC1101, 868 MHz), E22-900MM22S pad-compatible (spec 5.1)
TP101-TP107: 1.5 mm plated test pads, 0.7 mm hole, beside the radio bus (spec 5.5). R210 keeps the radio deselected while the ESP32 boots.
L1 bead on 3V3_RF: fit 0R (C17168) in its place for the E22 (100 mA TX: 0.11 V on the bead DCR).
C2 100 nF at U1 pin 1, C1 10 uF next to it (E07 DS 3.2, E22 DS 5.1).
U1 ANT -> R191 0R -> J1: 50 ohm grounded coplanar, 5-10 mm (spec 6.1).
C191 DNP: pi or low-pass position on the module side. L191 56 nH to GND: ESD path at J1 (review E01).
No tracks under U1 on any layer; top GND pour under the module, stitched to GND (E07 DS 4.1).
E22-900MM22S option (all links DNP; with the E07 fitted the NC pads touch nothing):
R101 NRST, R102 RXEN, R103 BUSY to their GPIOs; R104 TXEN (pad 9) to DIO2 (pad 19).
E07 GDO0 (18) = E22 DIO3, E07 GDO2 (20) = E22 DIO1. Pad table in spec 5.1.

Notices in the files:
README.md:
Licence:
Apache License 2.0. See [`LICENSE`](LICENSE) and [`NOTICE`](NOTICE).
